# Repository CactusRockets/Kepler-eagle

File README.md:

# Placas da aviônica para o foguete Kepler-200m

Nesse repositório temos os arquivos das placas que farão parte da aviônica do foguete Kepler de 200m da Cactus Rockets Design.

### Descrição

Temos duas placas principais para esta aviônica:
- Placa de Processamento
- Placa de Acionamento

A placa de processamento é responsável pelo processamento dos dados de altitude e pressão. A placa de acionamento possui o circuito necessário para a correta ativação do Skib.

OBS.: Os arquivos das placas podems ser abertos por meio software Eagle da Autodesk.

### Esquemáticos e layouts

### Conexões entre placas

### Funcionamento

A placa de processamento contém um switch de ativação do sistema. No momento que o switch é pressionado, o sistema liga e faz a leitura dos valores de pressão e altitude.

No momento que a placa de processamento detectar uma queda, ela envia um sinal para a placa de acionamento para que a mesma ative o Skib da parte de recuperação.

OBS.: Usa-se a memória EEPROM do arduino nano para armazenar o maior valor de altitude detectado pelo foguete.

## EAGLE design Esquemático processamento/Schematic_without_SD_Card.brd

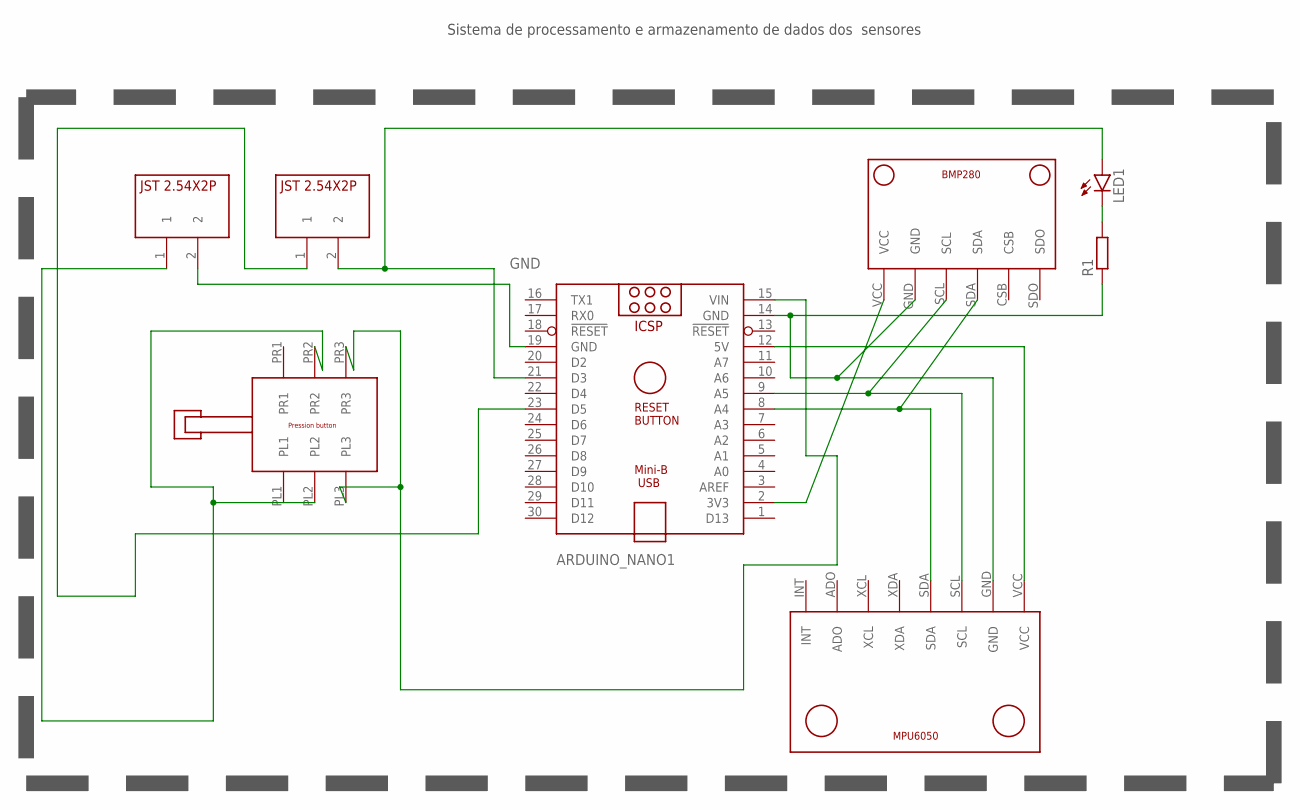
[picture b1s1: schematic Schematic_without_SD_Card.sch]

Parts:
ARDUINO_NANO1: ARDUINO_NANO
LED1: LED5MM
R1: R-EU_0207/10; 0207/10
U$1: BMP280V1; BMP280_FOOTPRINT
U$2: MPU6050V1; MPU6050_FOOTPRINT
U$3: PRESSION_BUTTON; PRESSION_BUTTON_FOOTPRINT
U$5, U$6: JST2.54X2P; JST2.54X2P_FOOTPRINT

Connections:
GND: ARDUINO_NANO1.14 (GND), ARDUINO_NANO1.19 (GND), R1.1, U$1.GND, U$2.GND, U$6.2
unnamed: ARDUINO_NANO1.2 (3V3), U$1.VCC
unnamed: ARDUINO_NANO1.9 (A5), U$1.SCL, U$1.SDO, U$2.SCL
unnamed: ARDUINO_NANO1.8 (A4), U$1.CSB, U$1.SDA, U$2.SDA
unnamed: ARDUINO_NANO1.15 (VIN), U$3.PL3, U$3.PR3
unnamed: ARDUINO_NANO1.12 (5V), U$2.VCC
unnamed: LED1.K (C), R1.2
unnamed: ARDUINO_NANO1.21 (D3), LED1.A, U$5.2
unnamed: ARDUINO_NANO1.23 (D5), U$5.1
VCC: U$3.PL1, U$3.PL2, U$3.PR2, U$6.1

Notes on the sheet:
Sistema de processamento e armazenamento de dados dos sensores

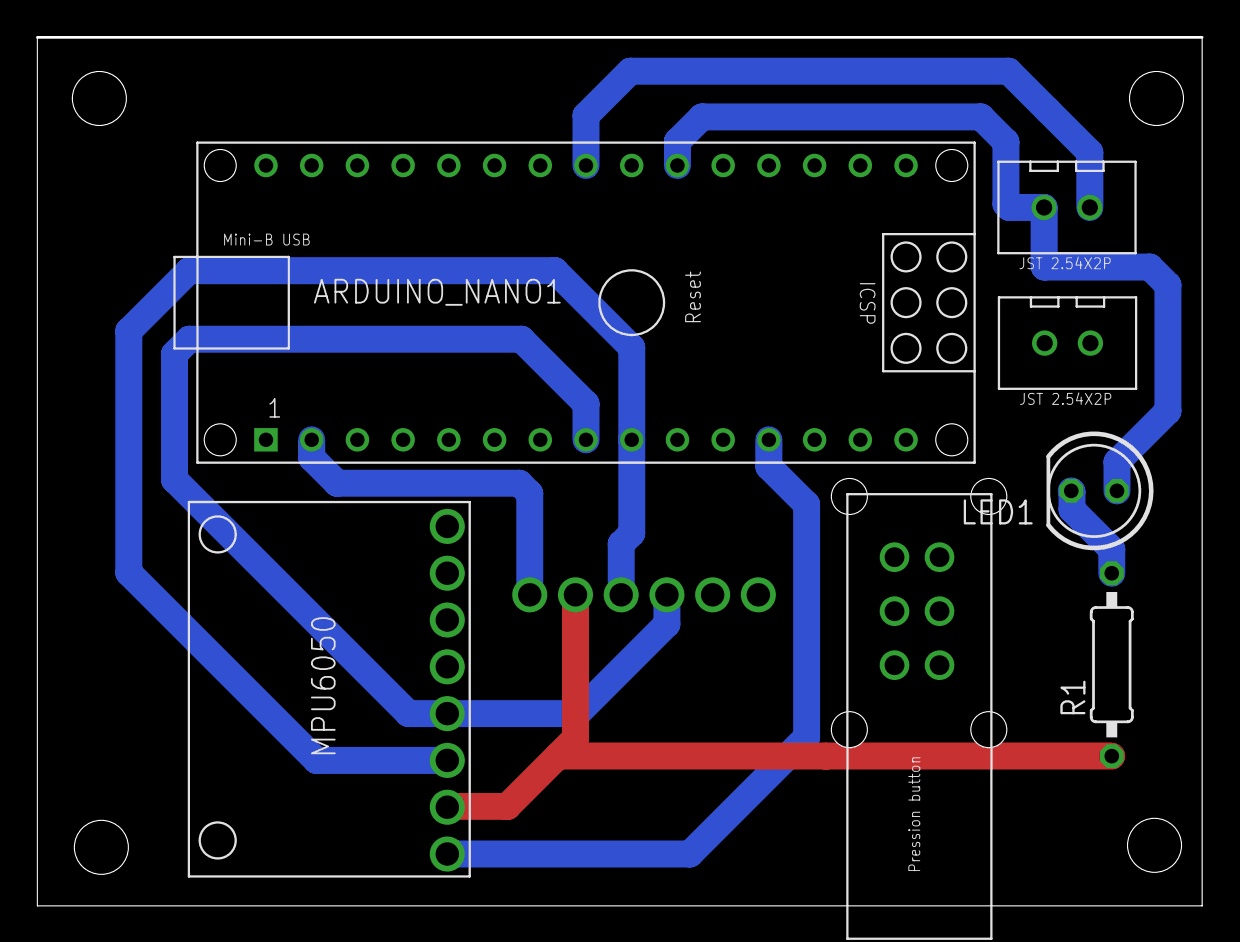
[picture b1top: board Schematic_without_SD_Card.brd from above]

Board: 2 copper layers, 64.7 x 48.2 mm, 8 parts (1 on the bottom side), 10 nets.

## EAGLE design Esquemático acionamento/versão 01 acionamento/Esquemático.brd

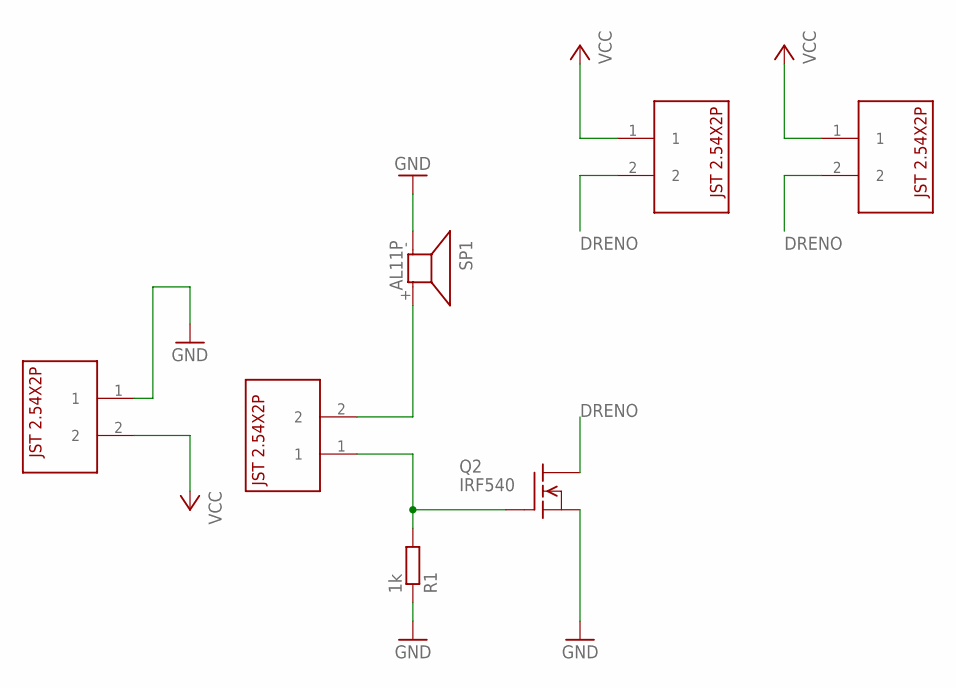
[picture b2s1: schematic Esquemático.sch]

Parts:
Q2: IRF540; TO220
R1: 1k; 0204/7
SP1: AL11P
U$1, U$2, U$3, U$4: JST2.54X2P; JST2.54X2P_FOOTPRINT

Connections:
DRENO: Q2.2 (D), U$2.2, U$3.2
GND: Q2.3 (S), R1.1, SP1.- (1), U$4.1
unnamed: Q2.1 (G), R1.2, U$1.1
unnamed: SP1.+ (2), U$1.2
VCC: U$2.1, U$3.1, U$4.2

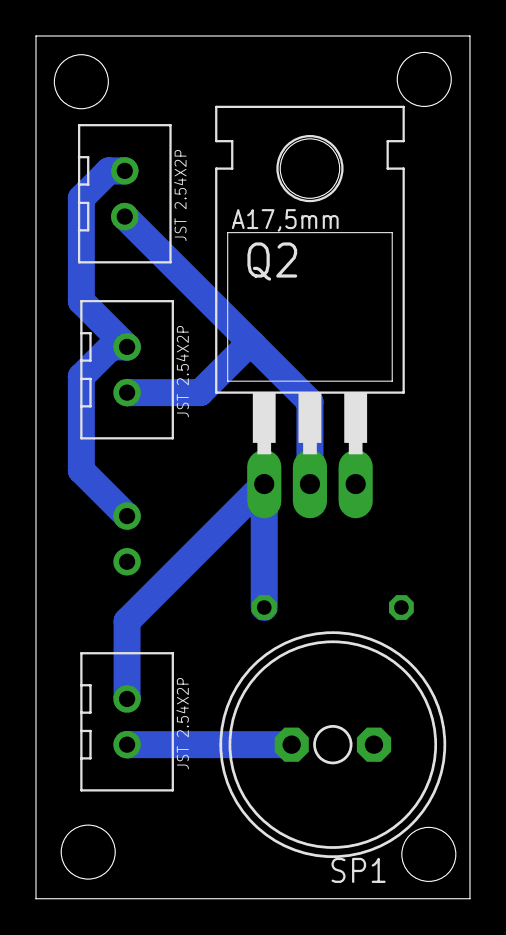
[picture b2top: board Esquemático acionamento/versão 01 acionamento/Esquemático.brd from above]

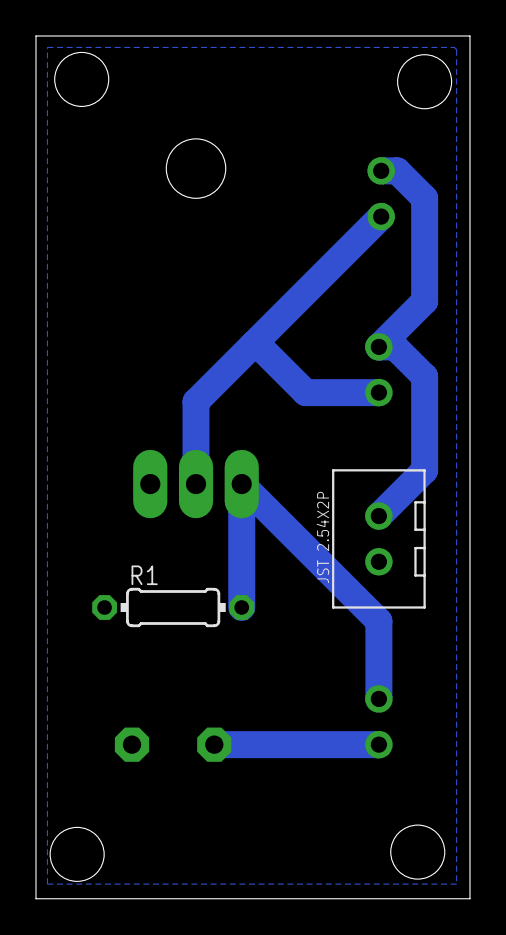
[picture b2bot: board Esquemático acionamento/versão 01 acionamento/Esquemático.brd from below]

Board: 2 copper layers, 24.1 x 47.9 mm, 7 parts (2 on the bottom side), 5 nets.

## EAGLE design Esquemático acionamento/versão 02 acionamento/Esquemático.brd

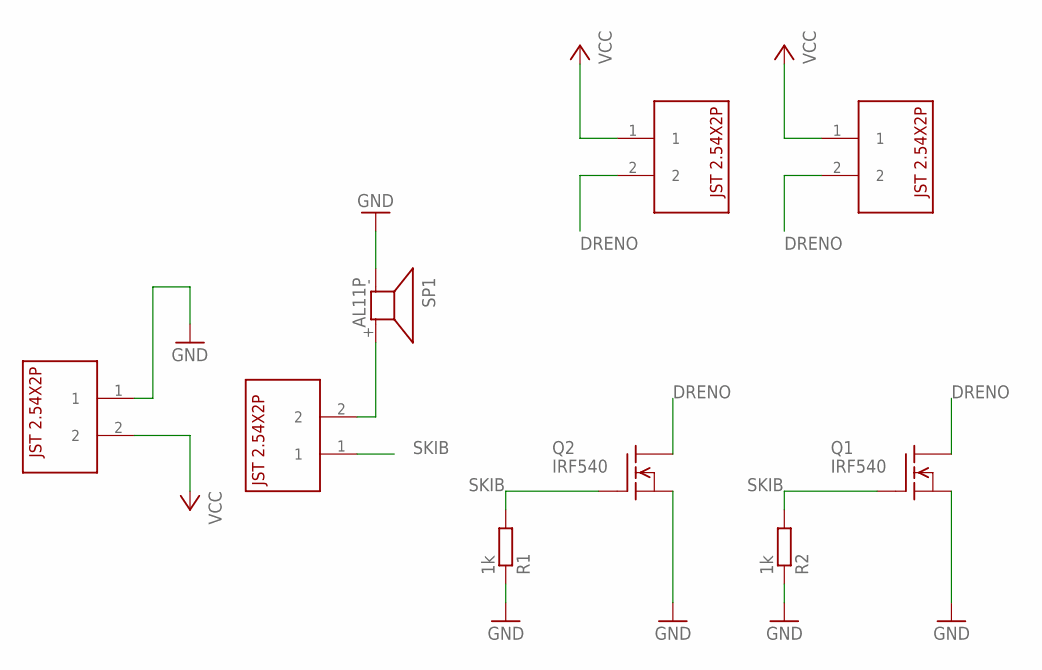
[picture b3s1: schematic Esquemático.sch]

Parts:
Q1, Q2: IRF540; TO220
R1, R2: 1k; 0204/7
SP1: AL11P
U$1, U$2, U$3, U$4: JST2.54X2P; JST2.54X2P_FOOTPRINT

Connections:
DRENO: Q1.2 (D), Q2.2 (D), U$2.2, U$3.2
GND: Q1.3 (S), Q2.3 (S), R1.1, R2.1, SP1.- (1), U$4.1
unnamed: SP1.+ (2), U$1.2
SKIB: Q1.1 (G), Q2.1 (G), R1.2, R2.2, U$1.1
VCC: U$2.1, U$3.1, U$4.2

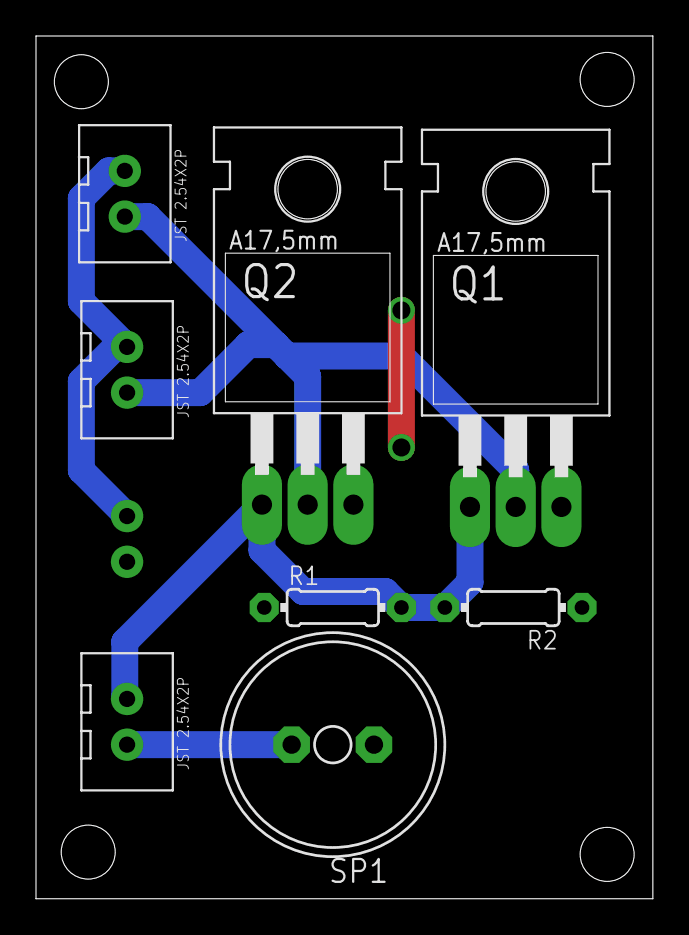
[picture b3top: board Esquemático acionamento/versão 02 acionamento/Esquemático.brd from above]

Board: 2 copper layers, 34.3 x 47.9 mm, 9 parts (1 on the bottom side), 5 nets.

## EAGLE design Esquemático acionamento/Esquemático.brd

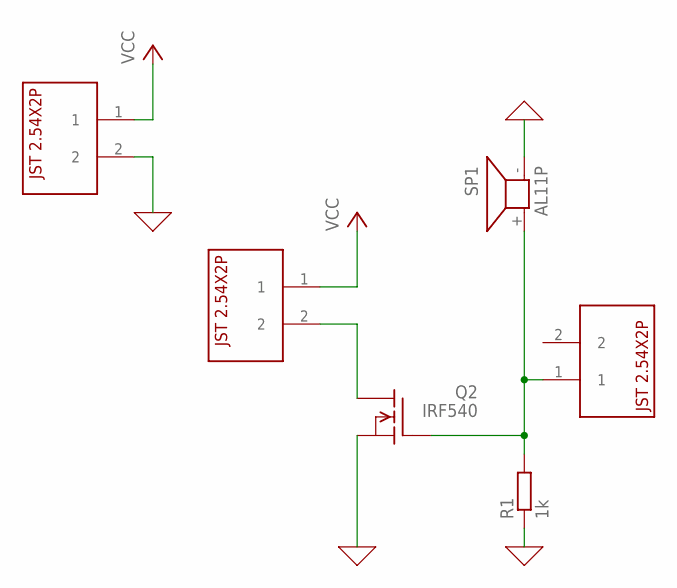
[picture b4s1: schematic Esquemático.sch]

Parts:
Q2: IRF540; TO220
R1: 1k; 0204/7
SP1: AL11P
U$1, U$2, U$4: JST2.54X2P; JST2.54X2P_FOOTPRINT

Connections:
0: Q2.3 (S), R1.1, SP1.- (1), U$4.2
unnamed: Q2.1 (G), R1.2, SP1.+ (2), U$1.1
unnamed: Q2.2 (D), U$2.2
VCC: U$4.1

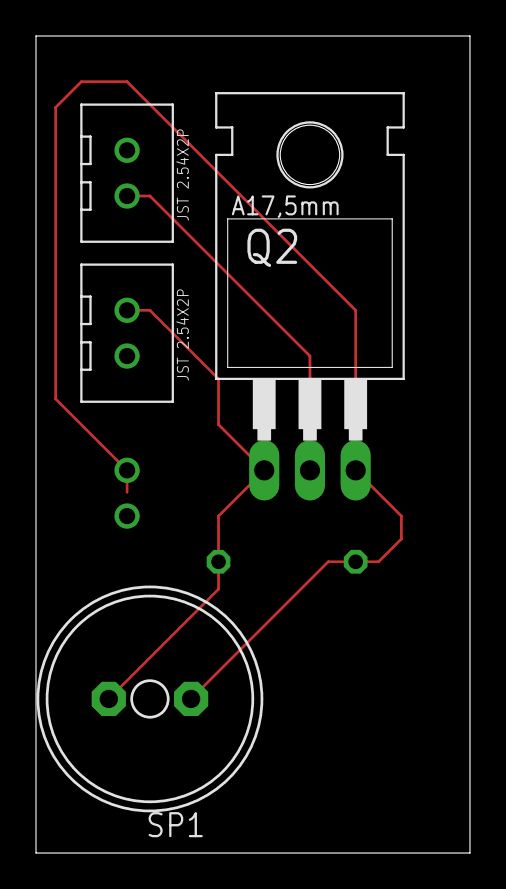
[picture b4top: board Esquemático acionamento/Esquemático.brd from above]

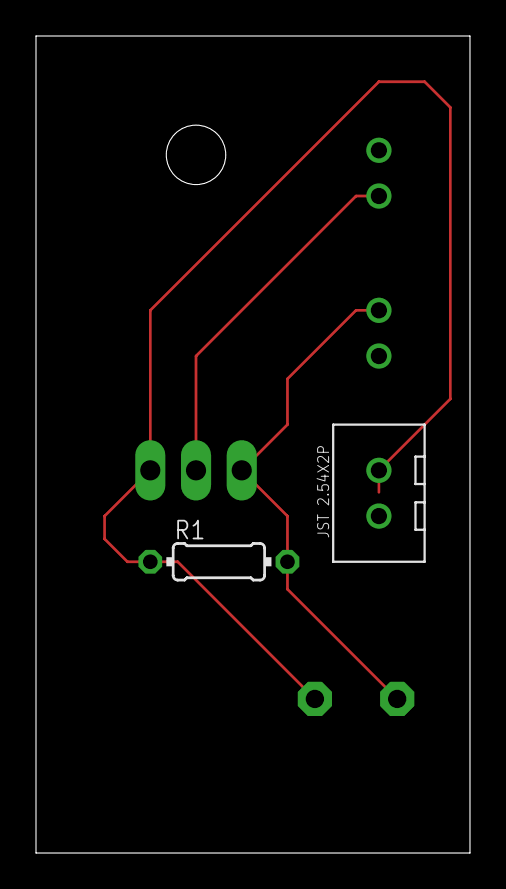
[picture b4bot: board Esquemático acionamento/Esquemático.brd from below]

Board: 2 copper layers, 24.1 x 45.4 mm, 6 parts (2 on the bottom side), 3 nets.

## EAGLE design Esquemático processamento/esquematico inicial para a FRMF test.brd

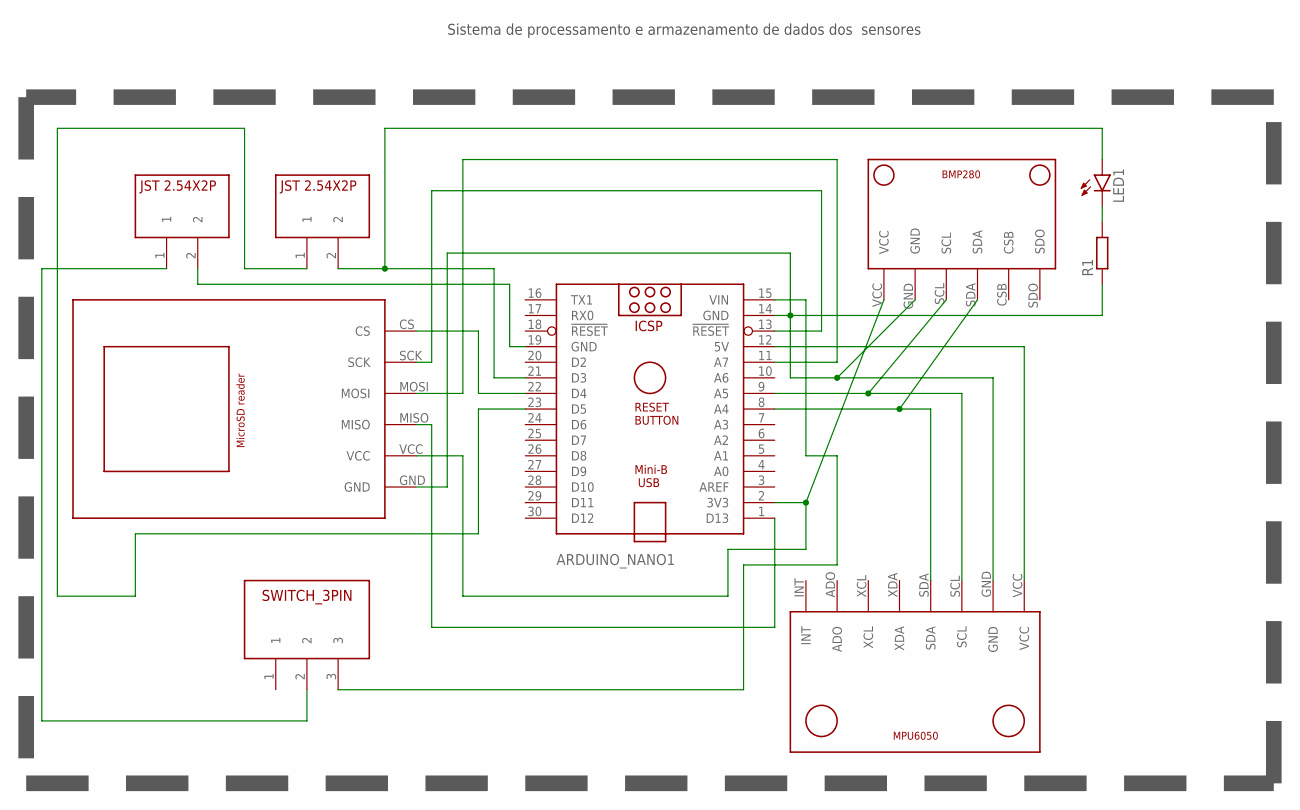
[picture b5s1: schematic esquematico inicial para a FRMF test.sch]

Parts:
ARDUINO_NANO1: ARDUINO_NANO
LED1: LED5MM
R1: R-EU_0207/10; 0207/10
U$1: BMP280V1; BMP280_FOOTPRINT
U$2: MPU6050V1; MPU6050_FOOTPRINT
U$3: MICROSD_READER; MICROSD_READER_FOOTPRINT
U$4: SWITCH_3PIN
U$5, U$6: JST2.54X2P; JST2.54X2P_FOOTPRINT

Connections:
unnamed: ARDUINO_NANO1.2 (3V3), U$1.VCC, U$3.VCC
unnamed: ARDUINO_NANO1.9 (A5), U$1.SCL, U$2.SCL
unnamed: ARDUINO_NANO1.8 (A4), U$1.SDA, U$2.SDA
unnamed: ARDUINO_NANO1.14 (GND), R1.1, U$1.GND, U$2.GND, U$3.GND
unnamed: ARDUINO_NANO1.12 (5V), U$2.VCC
unnamed: ARDUINO_NANO1.22 (D4), U$3.CS
unnamed: ARDUINO_NANO1.13 (!RESET), U$3.SCK
unnamed: ARDUINO_NANO1.11 (A7), U$3.MOSI
unnamed: ARDUINO_NANO1.1 (D13), U$3.MISO
unnamed: LED1.K (C), R1.2
unnamed: ARDUINO_NANO1.21 (D3), LED1.A, U$5.2
unnamed: ARDUINO_NANO1.19 (GND), U$6.2
unnamed: ARDUINO_NANO1.23 (D5), U$5.1
unnamed: ARDUINO_NANO1.15 (VIN), U$4.3
unnamed: U$4.2, U$6.1

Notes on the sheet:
Sistema de processamento e armazenamento de dados dos sensores

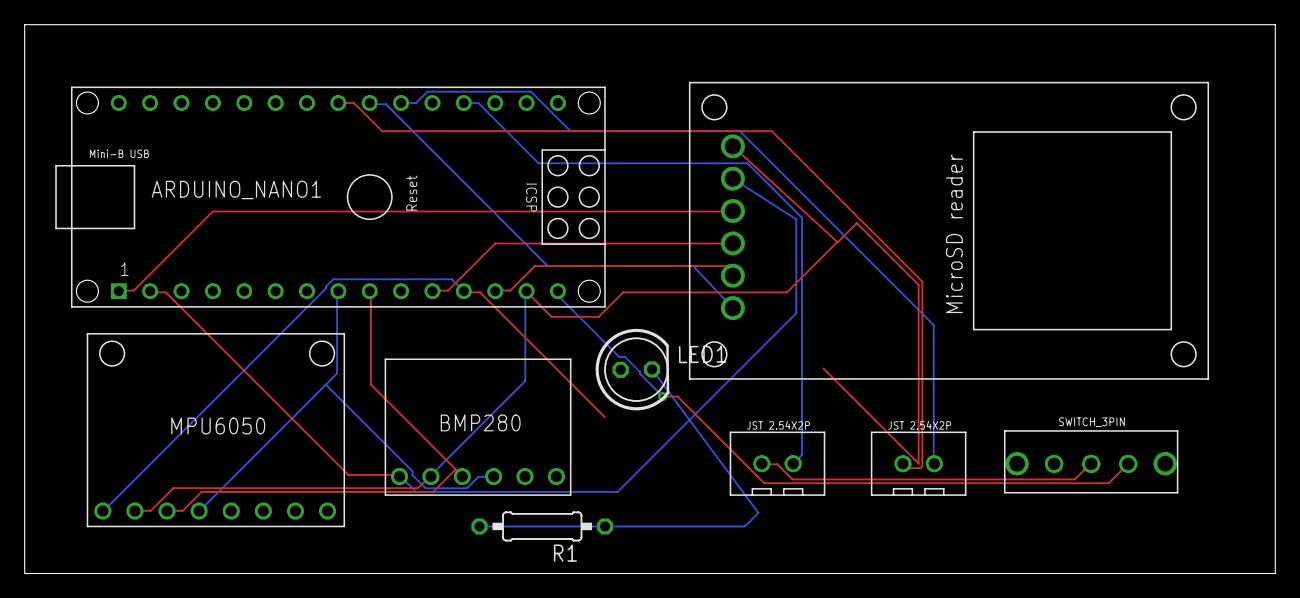
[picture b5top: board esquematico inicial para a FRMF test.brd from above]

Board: 2 copper layers, 101.3 x 44.4 mm, 9 parts (0 on the bottom side), 15 nets.

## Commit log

2024-02-23 Add files via upload
    Placa de Acionamento
2024-02-26 Melhorei a placa de acionamento
2024-02-27 Foi criada a Branch Alec
2024-02-27 Nova Placa Processamento
2024-02-27 resize wires and add holes
2024-02-28 Melhorei a placa de processamento
2024-02-29 Modificado footprint do botão
2024-02-29 Tamanho dos pads modificado (10mil - 30mil - 80%)
2024-02-29 adjusts
2024-02-29 Modificação
2024-03-02 Merge
